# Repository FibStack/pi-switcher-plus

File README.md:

# PiSwitcher Plus

## Overview

The **FibStack PiSwitcher Plus** board was designed to help you in your next automation project. 

The board has four high-quality relays allowing it to switch high voltage and currents. Controlling a steam iron or an oven is not the right task for the board, but it will handle most home appliances below 1200W. Each relay has an LED indicator showing when the NO (Normal Open) contact is connected to the COM (Common).

Additionally, the board has four 12-bit ADC channels that can convert electric signals up to 5 volts. The converted value allows more flexibility in the automation decision logic.

The FibStack Dashboard allows testing things on the fly without writing any code. Alternatively, you can control the board using the CLI tool or programmatically using provided libraries.
See the [Documentation](#documentation) section below for links to Getting Started guide and references.

## WARNING
**WARNING. Hazard of severe electrical shock or burn when using High Voltage/Current applications. Obey High Voltage/Current safety procedures. FibStack is not responsible for any damage or injury that occurs from improper High Voltage use.**

## Architecture

On the PiSwitcher Plus board, the ATTiny824 microcontroller receives commands from the RaspberryPi board through the I2C interface. 
The software package facilitates communication between the Raspberry Pi and the PiSwitcher Plus board. 

The `libfibstack` library is used by any library or tool directly or indirectly.
You can use the `libfistack` library directly in your C project. Please consult the [C API Reference](https://fibstack.com/piswitcher/c_api_ref/).

The `fibstackcli` is a convenient tool to get device statuses and switch relays from the command lines.

The `fibstacklib_cffi` is a Python wrapper around the `libfistack` library. We provide a `fibstacklibpy` library for convenience if you want to use it in your Python projects. See the [Python API Reference](https://fibstack.com/piswitcher/py_api_ref/).

The FibStack Dashboard is a convenient web-based UI tool that allows you to control the PiSwitcher Plus board. It consists of the back-end python script and a front-end project that uses Angular.

## Project organization

- **piswitcher_plus_board/**: this folder is a KiCAD project that contains FibStack PiSwitcher Plus board schematics and PCB layout files.
- **software/attiny824_switch_adc_board/**: This folder contains the Microchip Studio project with the source files for the ATTiny824 microcontroller. Note that the build will create the *.hex and *.eep files. Flash the ATTiny program memory with the *.hex file and the EEPROM memory with the *.eep file.
- **software/libfibstack/**: C library containing data structures and functions to communicate with the PiSwitcher Plus board.
- **software/fibstackcli/**: This folder contains the CLI tool source code.
- **software/fibstacklib_cffi/**: This folder contains the source code for the `libfibstack` library wrapper for Python.
- **software/fibstacklibpy/**: The Python library source code.
- **software/py_webapp/**: This folder contains the source code for the back-end service.
- **software/ng-webapp/**: This folder contains the source code for the FibStack Dashboard UI. The project uses Typescript and Angular framework.
- **software/installer/**: This folder contains scripts to install and uninstall the software package on the Raspberry Pi OS. The information on how to create the installation package will be added later.

## Development tools

- **[Microchip Studio 7.0](https://www.microchip.com/en-us/tools-resources/develop/microchip-studio)**: The IDE for writing and building source code for the ATTiny chip. We also use this tool to flash the chips.
- **[ATMEL-ICE](https://www.microchip.com/en-us/development-tool/ATATMEL-ICE)**: Hardware tool for flashing program and EEPROM memories.
- **[Python CFFI](https://cffi.readthedocs.io/en/latest)**: The Python wrapper library to build the `fibstacklib_cffi` project.
- **[Angular CLI 11.1.1](https://angular.io/cli)** To develop and build Angular projects.
- **Python 3.7 and up**
- Raspberry Pi OS **GCC** compiler

## BOM

| # | Components | Recommended models | Footprint | Quantity |
| --- | --- | --- | --- | --- |
| 1 | PCB | Recommended two-layer PCB board of 1.6 mm thickness | | 1 |
| 2 | U1 | ATTiny824-SSU | SOIC-14 package, 3.9x8.7mm pitch: 1.27mm | 1 |
| 3 | C1 | Any 100nF 50V SMD capacitor | 0805 (2012 metric) | 1 |
| 4 | Q1 - Q6 | 2N7002 N-channel MOSFET transistor, 60V 300mA | SOT-23-2| 6 |
| 5 | RL1 - RL4 | General purpose SPDT 5VDC relay. Recommended models J0971C, YX201-S-105D, or similar. | J0971C | 4 |
| 6 | D1 | SMD LED RED | 0603 (1608 metric) | 1 |
| 7 | D2, D3, D6, D7 | SMD LED GREEN | 0603 (1608 metric) | 4 |
| 8 | D4, D5, D8, D9 | Any general purpose SMD Diode, 75V, 200mA | MicroMELF | 4 |
| 9 | R1, R2, R3, R4, R5, R9, R10, R15, R16 | Any 10K 5% 1/4W SMD Resistor | 0603 (1608 metric) | 9 |
| 10 | R6, R7, R8, R11, R12, R13, R14, R17, R18 | Any 1K 5% 1/4W SMD Resistor | 0603 (1608 metric) | 9 |
| 11 | J1 | Extended GPIO Male Female Header, 2x20, pitch 2.54mm | 2x20 - P2.54mm | 1 |
| 12 | J2 | Optional, Male Header Connector, 2x3, pitch 2.54mm | 2x3 - P2.54mm | 1 |
| 13 | J3 | Male Header Connector, 1x6, pitch 2.54mm | 1x6 - P2.54mm | 1 |
| 14 | J4 | Screw Terminal Block 1x12, Pitch 3.5mm. Alternatively, you can use two of 1x6, three of 1x4, or four of 1x3. | 1x12 - P3.5mm | 1|

For the Extended GPIO Male Female header connector (J1), we recommend using a component as shown in the figure below. The female part has a height of 8.5mm plus two plastic pieces of 2.5mm. The female part is placed on the bottom of the board and soldered on the top of the board. The male pins should be 9.8mm or longer to allow an additional expansion board to be connected.

## Documentation
 - **[Project Home Page](https://fibstack.com/projects/piswitcher/)**
 - **[Getting Started Guide](https://fibstack.com/projects/piswitcher/get_started/)**
 - **[CLI Interface Tool](https://fibstack.com/projects/piswitcher/cli/)**
 - **[FibStack Dashboard](https://fibstack.com/projects/piswitcher/dashboard/)**
 - **[C API Reference](https://fibstack.com/projects/piswitcher/c_api_ref/)**
 - **[Python API Reference](https://fibstack.com/projects/piswitcher/py_api_ref/)**

## I2C Protocol

The software package communicates with PiSwitcher Plus through the I2C (or IIC, TWI) interface. Theoretically, you can send the instructions from any device that supports the I2C interface.
We developed a simple protocol that uses only five commands for now. 
You can write your software to control the board using the commands below.

| # | Command | Description |
| --- | --- | --- |
| 1 | `version` | Returns a constant string from the board that represents the Firmware/Hardware version. |
| 2 | `setaddr:<new_address_value>` | Set the PiSwitcher Plus board I2C address. The valid address value should be an integer between 3 and 119. |
| 3 | `status` | Returns a set of values delimited by a colon `:`. Each value represents a device value. The first four values represent the Relay values, `1 `means the relay's coil is energized, `0` otherwise. The last four values represent the values from ADC channels. Example: `0:1:1:0:120:1023:0:785`. |
| 4 | `get:<device_id>` | Returns the value (status) for the specified device. The relay devices IDs are from 0 to 3 inclusive. The ADC channel device IDs are from 4 to 7 inclusive. |
| 5 | `set:<device_id>:<value>` | Sets the value for the specified device. This command is used to switch relay devices on the PiSwitcher Plus board. The `set` command doesn't work for ADC devices as they are Read-Only. The valid values for the `device_id` are from 0 to 3 inclusive. The possible values are 0 and 1. |

## License Information
This product is open source!

Please review the LICENSE.md file for license information. Distributed as-is; no warranty is given.

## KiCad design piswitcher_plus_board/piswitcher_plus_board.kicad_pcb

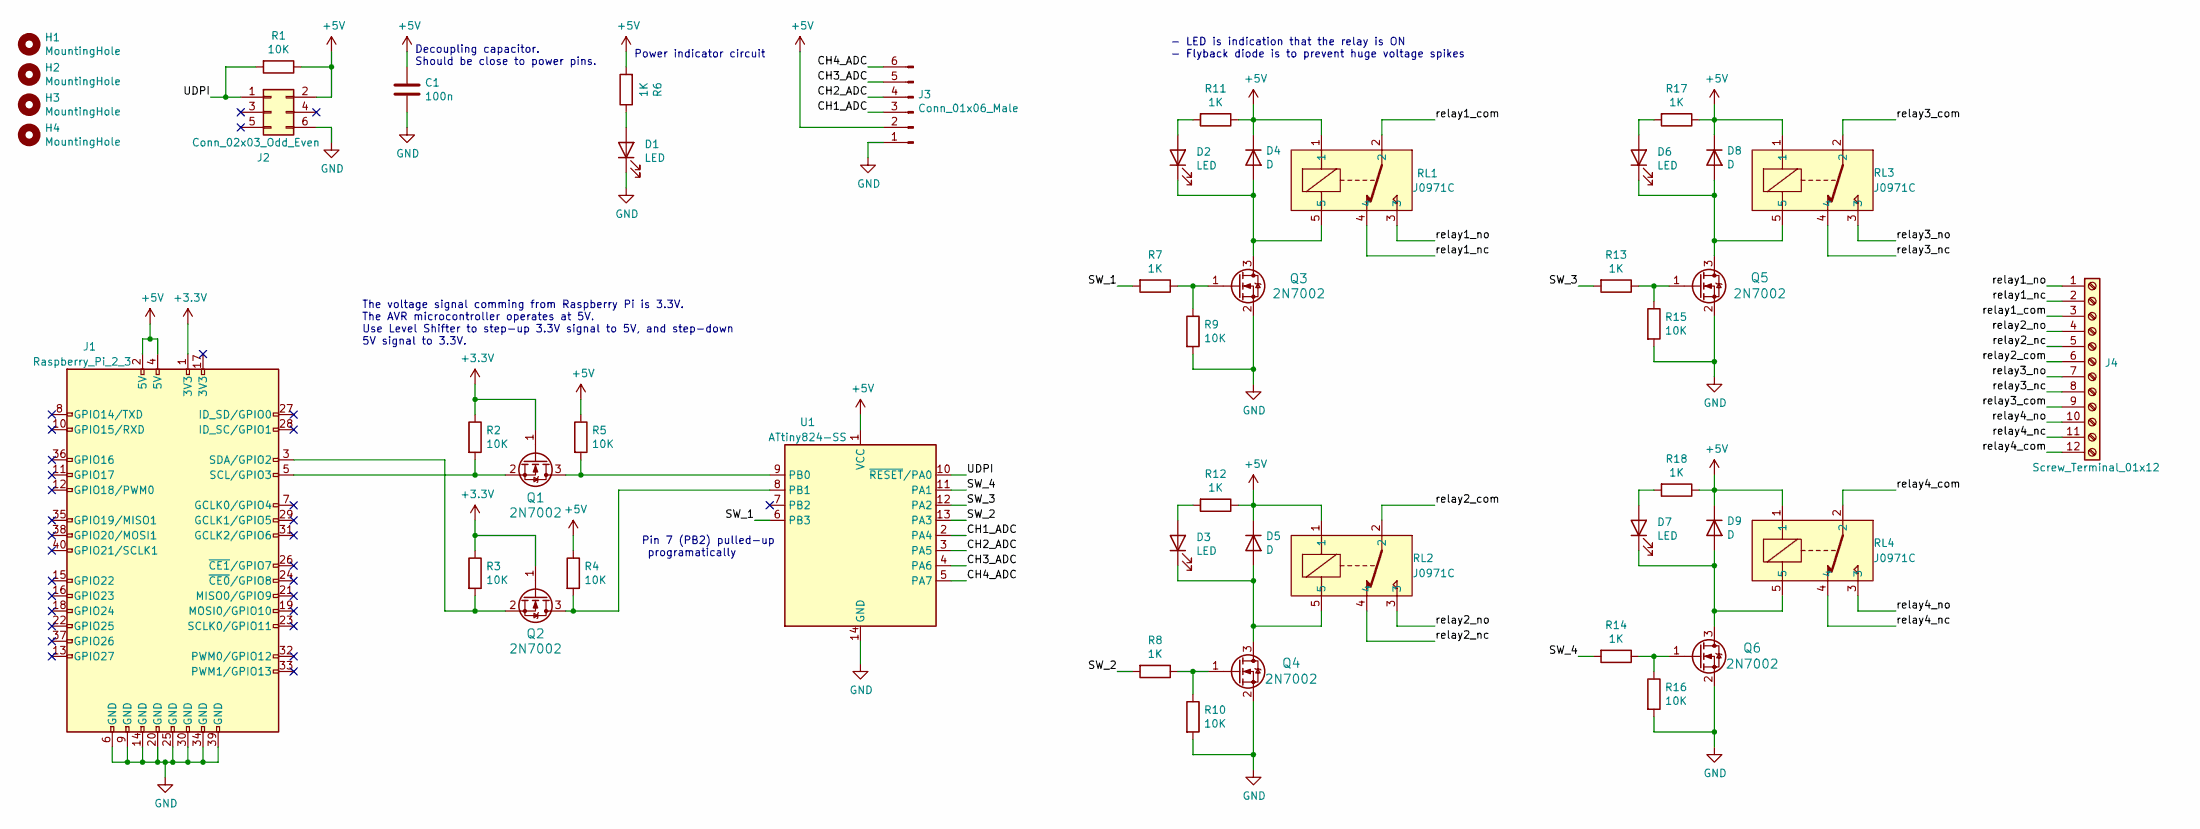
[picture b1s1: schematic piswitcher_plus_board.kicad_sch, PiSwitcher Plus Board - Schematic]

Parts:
C1: 100n; C_0805_2012Metric
D1, D2, D3, D6, D7: LED; LED_0603_1608Metric
D4, D5, D8, D9: D; D_MicroMELF
H1, H2, H3, H4: MountingHole; CustomMountingHole
J1: Raspberry_Pi_2_3; PinHeader_2x20_P2.54mm_Vertical
J2: Conn_02x03_Odd_Even; PinHeader_2x03_P2.54mm_Vertical
J3: Conn_01x06_Male; PinHeader_1x06_P2.54mm_Vertical
J4: Screw_Terminal_01x12; TerminalBlock_4Ucon_1x12_P3.50mm_Horizontal
Q1, Q2, Q3, Q4, Q5, Q6: 2N7002; SOT-23-3
R1, R2, R3, R4, R5, R9, R10, R15, R16: 10K; R_0603_1608Metric
R6, R7, R8, R11, R12, R13, R14, R17, R18: 1K; R_0603_1608Metric
RL1, RL2, RL3, RL4: J0971C
U1: ATtiny824-SS; SOIC-14_3.9x8.7mm_P1.27mm

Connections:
+3V3: J1.1 (3V3), Q1.1 (G), Q2.1 (G), R2.1, R3.1
+5V: C1.1, D4.1 (K), D5.1 (K), D8.1 (K), D9.1 (K), J1.2 (5V), J1.4 (5V), J2.2, J3.2, R1.1, R4.1, R5.1, R6.2, R11.1, R12.1, R17.1, R18.1, RL1.1, RL2.1, RL3.1, RL4.1, U1.1 (VCC)
/CH1_ADC: J3.3, U1.2 (PA4)
/CH2_ADC: J3.4, U1.3 (PA5)
/CH3_ADC: J3.5, U1.4 (PA6)
/CH4_ADC: J3.6, U1.5 (PA7)
/SW_1: R7.2, U1.6 (PB3)
/SW_2: R8.2, U1.13 (PA3)
/SW_3: R13.2, U1.12 (PA2)
/SW_4: R14.2, U1.11 (PA1)
/UDPI: J2.1, R1.2, U1.10 (~RESET/PA0)
/relay1_com: J4.3, RL1.2
/relay1_nc: J4.2, RL1.4
/relay1_no: J4.1, RL1.3
/relay2_com: J4.6, RL2.2
/relay2_nc: J4.5, RL2.4
/relay2_no: J4.4, RL2.3
/relay3_com: J4.9, RL3.2
/relay3_nc: J4.8, RL3.4
/relay3_no: J4.7, RL3.3
/relay4_com: J4.12, RL4.2
/relay4_nc: J4.11, RL4.4
/relay4_no: J4.10, RL4.3
GND: C1.2, D1.1 (K), J1.6 (GND), J1.9 (GND), J1.14 (GND), J1.20 (GND), J1.25 (GND), J1.30 (GND), J1.34 (GND), J1.39 (GND), J2.6, J3.1, Q3.2 (S), Q4.2 (S), Q5.2 (S), Q6.2 (S), R9.2, R10.2, R15.2, R16.2, U1.14 (GND)
unnamed: D1.2 (A), R6.1
unnamed: D2.1 (K), D4.2 (A), Q3.3 (D), RL1.5
unnamed: D2.2 (A), R11.2
unnamed: D3.1 (K), D5.2 (A), Q4.3 (D), RL2.5
unnamed: D3.2 (A), R12.2
unnamed: D6.1 (K), D8.2 (A), Q5.3 (D), RL3.5
unnamed: D6.2 (A), R17.2
unnamed: D7.1 (K), D9.2 (A), Q6.3 (D), RL4.5
unnamed: D7.2 (A), R18.2
unnamed: J1.3 (SDA/GPIO2), Q2.2 (S), R3.2
unnamed: J1.5 (SCL/GPIO3), Q1.2 (S), R2.2
unnamed: Q1.3 (D), R5.2, U1.9 (PB0)
unnamed: Q2.3 (D), R4.2, U1.8 (PB1)
unnamed: Q3.1 (G), R7.1, R9.1
unnamed: Q4.1 (G), R8.1, R10.1
unnamed: Q5.1 (G), R13.1, R15.1
unnamed: Q6.1 (G), R14.1, R16.1

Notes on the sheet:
- LED is indication that the relay is ON - Flyback diode is to prevent huge voltage spikes
Power indicator circuit
Decoupling capacitor. Should be close to power pins.
The voltage signal comming from Raspberry Pi is 3.3V. The AVR microcontroller operates at 5V. Use Level Shifter to step-up 3.3V signal to 5V, and step-down 5V signal to 3.3V.
Pin 7 (PB2) pulled-up programatically

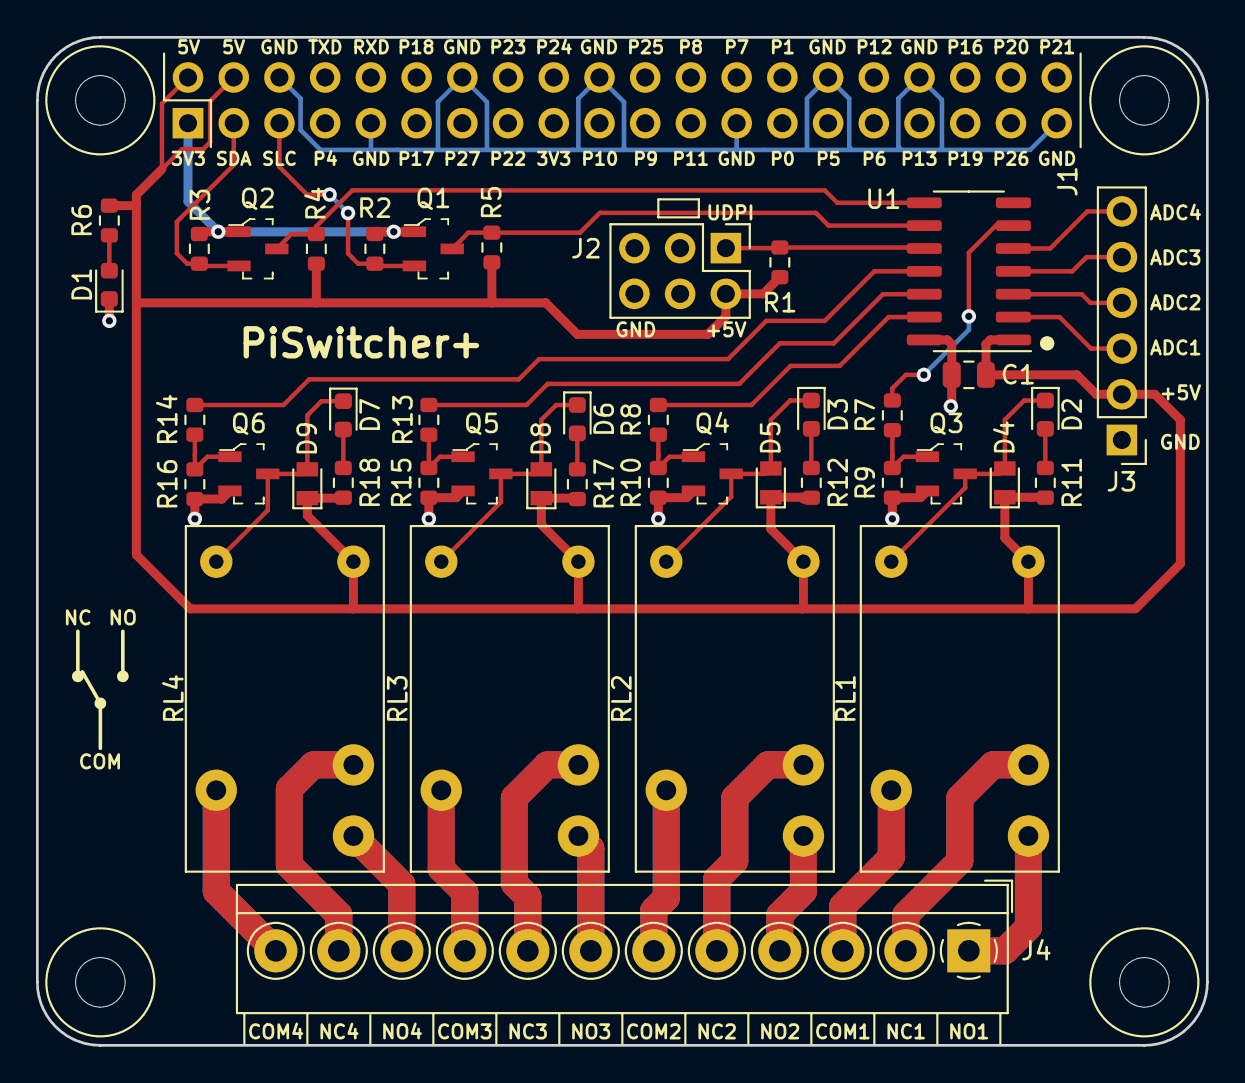
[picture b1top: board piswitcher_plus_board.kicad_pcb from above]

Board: 2 copper layers, 65.0 x 56.0 mm, 47 parts (0 on the bottom side), 41 nets.

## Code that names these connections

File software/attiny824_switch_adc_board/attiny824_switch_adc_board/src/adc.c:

/*
* Copyright (c) 2021, FibStack
* All rights reserved.
* 
* This source code is licensed under the MIT license found in the
* LICENSE file in the root directory of this source tree. 
*/

#include <xc.h>
#include "adc.h"

uint16_t adc_result[ADC_CHANNELS] = { 0, 0, 0, 0};
uint8_t adc_muxpos[ADC_CHANNELS] = {ADC_MUXPOS_AIN4_gc, ADC_MUXPOS_AIN5_gc, ADC_MUXPOS_AIN6_gc, ADC_MUXPOS_AIN7_gc};
uint8_t adc_channel = 0;

void ADC0_init()
{
	// Disable digital input buffer PA4 (pin 2), ADC channel 1
	PORTA.PIN4CTRL &= ~PORT_ISC_gm;
	PORTA.PIN4CTRL |= PORT_ISC_INPUT_DISABLE_gc;

	// Disable digital input buffer PA5 (pin 3), ADC channel 2
	PORTA.PIN5CTRL &= ~PORT_ISC_gm;
	PORTA.PIN5CTRL |= PORT_ISC_INPUT_DISABLE_gc;
	
	// Disable digital input buffer PA6 (pin 4), ADC channel 3
	PORTA.PIN6CTRL &= ~PORT_ISC_gm;
	PORTA.PIN6CTRL |= PORT_ISC_INPUT_DISABLE_gc;

	// Disable digital input buffer PA7 (pin 5), ADC channel 4
	PORTA.PIN7CTRL &= ~PORT_ISC_gm;
	PORTA.PIN7CTRL |= PORT_ISC_INPUT_DISABLE_gc;

	// Disable pull-up resistor
	PORTA.PIN4CTRL &= ~PORT_PULLUPEN_bm; // ADC channel 1
	PORTA.PIN5CTRL &= ~PORT_PULLUPEN_bm; // ADC channel 2
	PORTA.PIN6CTRL &= ~PORT_PULLUPEN_bm; // ADC channel 3
	PORTA.PIN7CTRL &= ~PORT_PULLUPEN_bm; // ADC channel 4
	
	ADC0.COMMAND = ADC_MODE_SINGLE_12BIT_gc;


	ADC0.CTRLC = ADC_PRESC_DIV4_gc		// CKL_PER divided by 4
	| ADC_REFSEL_VDD_gc; // VDD reference

	ADC0.CTRLA |= ADC_ENABLE_bm; // Enable ADC
	ADC0.MUXPOS = adc_muxpos[adc_channel]; // Select first channel

	ADC0.INTCTRL |= ADC_RESRDY_bm; // Enable Result Ready interrupt
	
}

void ADC0_start()
{
	ADC0.COMMAND |= ADC_START_IMMEDIATE_gc; // Start conversion
}

void ADC0_clear_interrupt_flag()
{
	ADC0.INTFLAGS = ADC_RESRDY_bm; // Clear the ADC Result Ready interrupt flag by writing 1
}

void ADC0_process()
{
	ADC0_clear_interrupt_flag();
	
	adc_result[adc_channel] = ADC0.SAMPLE;
	adc_channel++;
	
	// reset the current channel
	if(adc_channel >= ADC_CHANNELS)
	{
		adc_channel = 0;
	}
	
	ADC0.MUXPOS = adc_muxpos[adc_channel];
	
	ADC0_start();
}

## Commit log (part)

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2022-10-14 Initial commit with the files from old repo
2022-10-16 Converted the kicad5 project to kicad6 project
2022-10-16 Initial code clean up
2022-10-16 Ng update performed
2022-10-16 Minor sonnar issue fixes
2022-10-16 Fixed more sonar issues
2022-10-16 Fixed sonar issue
2022-10-16 Updated header files
2022-10-24 Wrote the README.md, LICENSE.md, and other modifications
2022-10-24 Minor changes to the README
2022-11-08 Updated text from Fibstack to FibStack, updated readme
2022-11-08 Added the image
2022-11-17 Created basic Jenkins file
2022-11-17 added new command
2022-11-17 testing script permisions
2022-11-17 Make installation script files executable
2022-11-17 Checking nodejs
2022-11-17 Specified nodejs tool
2022-11-17 Front end build attempt
2022-11-17 Fixed syntax
2022-11-17 Copy backend and C library files
2022-11-17 fixed folder names
2022-11-18 Testing copying all the files in the installer folder
2022-11-18 testing tar.gz file creation
2022-11-18 Test downloading makeself utility
2022-11-18 Trying http_request plugin
2022-11-18 Fixing errors
2022-11-18 install utility script
2022-11-18 try tar.gz archive
2022-11-18 try changing file encoding
2022-11-18 testing curl
2022-11-18 testing downloaded file
2022-11-18 Fixed file dowloading from github
2022-11-18 Test building the package
2022-11-18 Final cleanup
2022-11-20 Jenkins pipeline file (#1)
    Created Jenkinsfile to streamline the installation package build.
2023-01-03 Updated links
2023-01-03 Updated links (#2)
2023-01-03 Merging most updated code to master (#3)
    * Initial commit with the files from old repo
    * Converted the kicad5 project to kicad6 project
    * Initial code clean up
    * Ng update performed
    * Minor sonnar issue fixes
    * Fixed more sonar issues
2023-01-05 Updated link to the dashboard documentation
2023-01-05 Updated link to the dashboard documentation (#4)
2023-03-11 Bump minimist from 1.2.5 to 1.2.8 in /software/ng-webapp
    Bumps [minimist](https://github.com/minimistjs/minimist) from 1.2.5 to 1.2.8.
    - [Release notes](https://github.com/minimistjs/minimist/releases)
    - [Changelog](https://github.com/minimistjs/minimist/blob/main/CHANGELOG.md)
    - [Commits](https://github.com/minimistjs/minimist/compare/v1.2.5...v1.2.8)
    ---
    updated-dependencies:
2023-03-13 Fixed the build configuration. Tested build
2023-03-13 Bump minimist from 1.2.5 to 1.2.8 in /software/ng-webapp (#6)
    * Bump minimist from 1.2.5 to 1.2.8 in /software/ng-webapp
    Bumps [minimist](https://github.com/minimistjs/minimist) from 1.2.5 to 1.2.8.
    - [Release notes](https://github.com/minimistjs/minimist/releases)
    - [Changelog](https://github.com/minimistjs/minimist/blob/main/CHANGELOG.md)
    - [Commits](https://github.com/minimistjs/minimist/compare/v1.2.5...v1.2.8)
    ---
2023-03-15 upgrade to Angular 15
2023-03-15 Updated angular build command in Jenkinsfile
2023-03-15 Updated the installer version
2023-03-15 Angular 15 upgrade (#7)
    * upgrade to Angular 15
    * Updated angular build command in Jenkinsfile
    * Updated the installer version
2023-03-15 Fixed the dashboard ui folder name
2023-03-15 Fixed the dashboard ui folder name (#9)
2023-03-15 Angular 15 upgrade (#7) (#8)
    * Angular 15 upgrade (#7)
    * upgrade to Angular 15
    * Updated angular build command in Jenkinsfile
    * Updated the installer version
    * Fixed the dashboard ui folder name (#9)
2023-03-26 updated angular/cli
2023-03-26 Updated angular/core
2023-03-26 Updating vulnerable dependencies (#10)
    * updated angular/cli
    * Updated angular/core
2023-05-28 upgraded angular/core
2023-05-28 upgraded angular/cli version
2023-05-28 updated karma dependency
2023-05-28 updated dependencies
2023-05-28 Security/udates (#11)
    * upgraded angular/core
    * upgraded angular/cli version
    * updated karma dependency
    * updated dependencies
2023-06-18 updated @angular/core
2023-06-18 updated @angular/cli dependency
2023-06-18 Upgraded dependencies
2023-06-18 Vite vulnerability fix (#12)
    * updated @angular/core
    * updated @angular/cli dependency
    * Upgraded dependencies
2023-08-14 Upgraded packages
2023-08-14 Upgraded packages to fix a critical vulnerability (#13)
    * updated angular/core
    * updated angular/cli
    * Upgraded packages
2023-10-22 Upgraded angular packages
2023-10-22 Upgraded angular packages (#14)
2023-10-22 regenerated package-lock.json
2023-10-22 Dependencies/upgrade (#15)
    * Upgraded angular packages
    * regenerated package-lock.json
2024-01-21 Upgraded angular libraries
2024-01-21 Updated tslib and jasmine libraries
2024-02-18 Upgraded angular-core
2024-02-18 version libs update
2024-02-18 Feature/lib upgrade (#18)
    * Upgraded angular/core
    * Upgraded angular-core
    * version libs update
2024-02-25 upgraded ng cli
2024-02-25 upgraded ng/core
2024-02-25 updated karma lib
2024-02-25 Dependencies upgrade (#19)
    * upgraded ng cli
    * upgraded ng/core
    * updated karma lib
2024-03-11 upgraded angluar/cli
2024-03-11 angular cli and core upgrade (#20)
    * upgraded angluar/cli
    * upgraded ng/core
2024-03-31 Upgraded ng
2024-03-31 ng core update
2024-03-31 Upgraded typebscript
2024-03-31 Upgraded ng and typescript dependencies (#21)
    * Upgraded ng
    * ng core update
    * Upgraded typebscript
2024-04-29 updated typescript dep
2024-04-29 Updating @angular cli and core (#22)
    * Upgraded ng
    * ng core update
    * Upgraded typebscript
    * updated angular/cli
    * updated angular/core
    * updated typescript dep
2024-05-26 Migrated to the latest angular
2024-05-26 Upgraded zone and another dependency
2024-06-30 Updated ng/cli
2024-07-28 updated cli
2024-07-28 updated ng core
2024-07-28 Upgraded additional libraries
2024-08-28 updated additional dependencies
2024-10-28 cli lib upgrade
2024-10-28 package-lock.json update
2024-11-30 upgraded angular
2025-02-07 upgraded angluar cli and core dependencies
2025-02-07 updated other dependencies
2025-04-05 Upgraded ng/cli
2025-04-05 Updated ng/core
2025-05-11 ugrading libs
2025-08-03 updated angular dependencies
2025-10-05 Updating dependencies
2025-12-28 ng cli upgrade
2025-12-28 Updated jasmine dependency
2026-02-28 Upgraded angular/cli
2026-02-28 Fixed vulns

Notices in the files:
piswitcher_plus_board/piswitcher_plus_board.kicad_pcb:
of the CERN-OHL-P V2 license (https:/cern.ch/cern-ohl).
Copyright © 2021-2022, FibStack
